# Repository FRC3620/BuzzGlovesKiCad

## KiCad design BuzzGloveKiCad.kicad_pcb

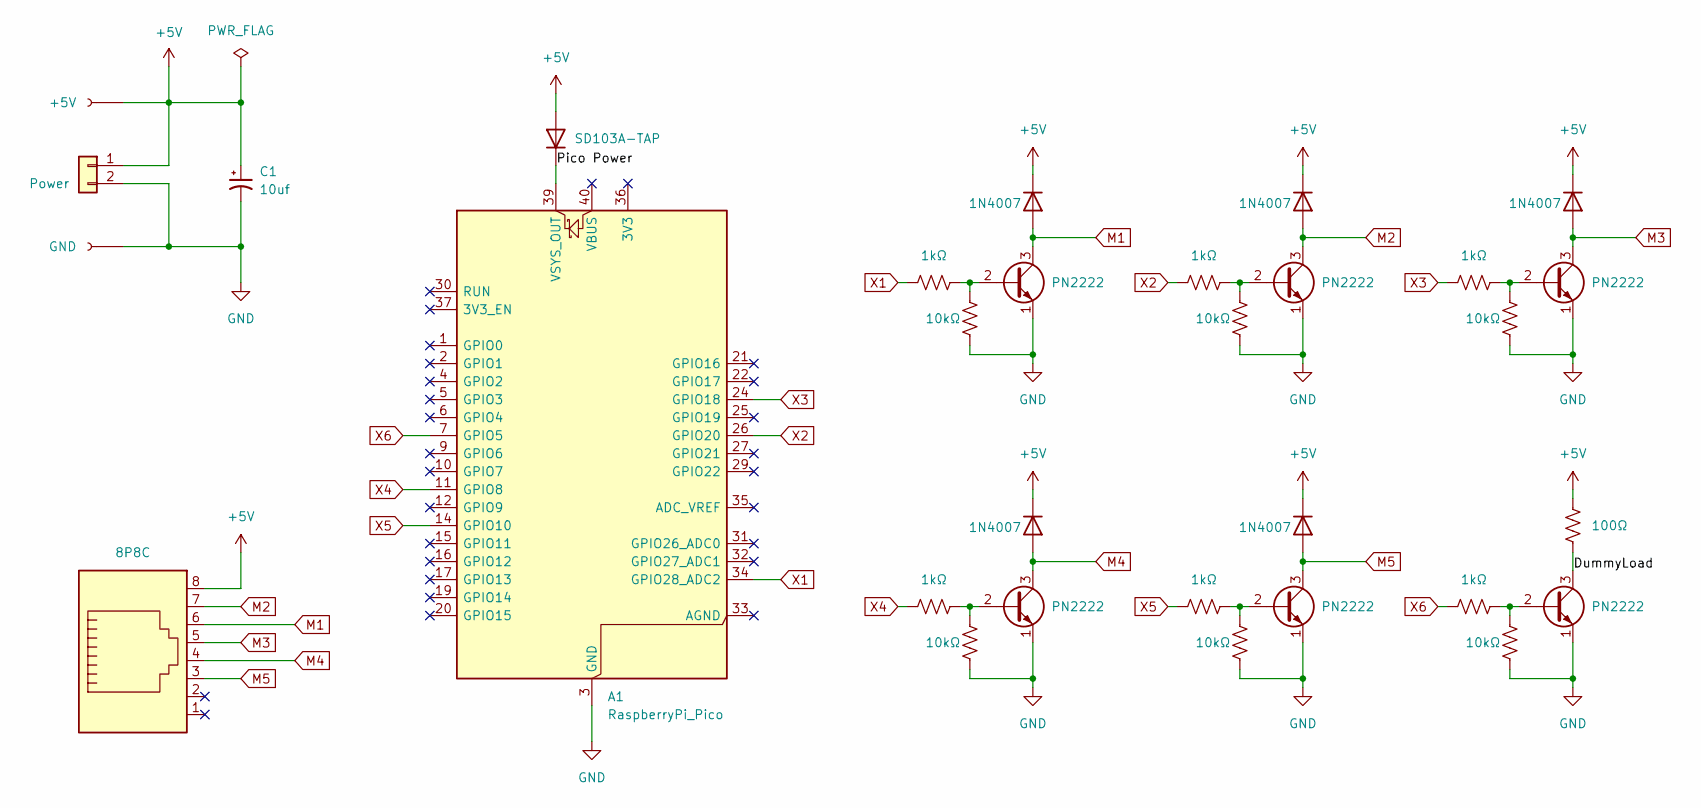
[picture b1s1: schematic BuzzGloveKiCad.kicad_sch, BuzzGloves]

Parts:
A1: RaspberryPi_Pico; RaspberryPi_Pico_Common_Unspecified
C1: 10uf; CP_Radial_D6.3mm_P2.50mm
D1: SD103A-TAP; D_DO-35_SOD27_P7.62mm_Horizontal
D2, D3, D4, D5, D6: 1N4007; D_DO-41_SOD81_P10.16mm_Horizontal
J1: +5V; Pin_D1.0mm_L10.0mm
J2: 8P8C; AMPHENOL_54602-908LF
J3: GND; Pin_D1.0mm_L10.0mm
J4: Power; JST_PH_B2B-PH-K_1x02_P2.00mm_Vertical
Q1, Q2, Q3, Q4, Q5, Q6: PN2222; TO-92
R3, R5, R7, R9, R11, R13: 1kΩ; R_Axial_DIN0204_L3.6mm_D1.6mm_P7.62mm_Horizontal
R4, R6, R8, R10, R12, R14: 10kΩ; R_Axial_DIN0204_L3.6mm_D1.6mm_P7.62mm_Horizontal
R15: 100Ω; R_Axial_DIN0207_L6.3mm_D2.5mm_P10.16mm_Horizontal

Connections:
+5V: C1.1, D1.2 (A), D2.1 (K), D3.1 (K), D4.1 (K), D5.1 (K), D6.1 (K), J1.1, J2.8, J4.1, R15.1
/DummyLoad: Q6.3 (C), R15.2; also elsewhere on the board
/Pico Power: A1.39 (VSYS_OUT), D1.1 (K)
GND: A1.3 (GND), A1.8 (GND), A1.13 (GND), A1.18 (GND), A1.23 (GND), A1.28 (GND), A1.38 (GND), C1.2, J3.1, J4.2, Q1.1 (E), Q2.1 (E), Q3.1 (E), Q4.1 (E), Q5.1 (E), Q6.1 (E), R4.2, R6.2, R8.2, R10.2, R12.2, R14.2; also elsewhere on the board
M1: D2.2 (A), J2.6, Q1.3 (C)
M2: D3.2 (A), J2.7, Q2.3 (C)
M3: D4.2 (A), J2.5, Q3.3 (C)
M4: D5.2 (A), J2.4, Q4.3 (C)
M5: D6.2 (A), J2.3, Q5.3 (C)
unnamed: Q1.2 (B), R3.1, R4.1
unnamed: Q2.2 (B), R5.1, R6.1
unnamed: Q3.2 (B), R7.1, R8.1
unnamed: Q4.2 (B), R9.1, R10.1
unnamed: Q5.2 (B), R11.1, R12.1
unnamed 14: Q6.2 (B), R13.1, R14.1; also elsewhere on the board
X1: A1.34 (GPIO28_ADC2), R3.2
X2: A1.26 (GPIO20), R5.2
X3: A1.24 (GPIO18), R7.2
X4: A1.11 (GPIO8), R9.2
X5: A1.14 (GPIO10), R11.2
X6: A1.7 (GPIO5), R13.2

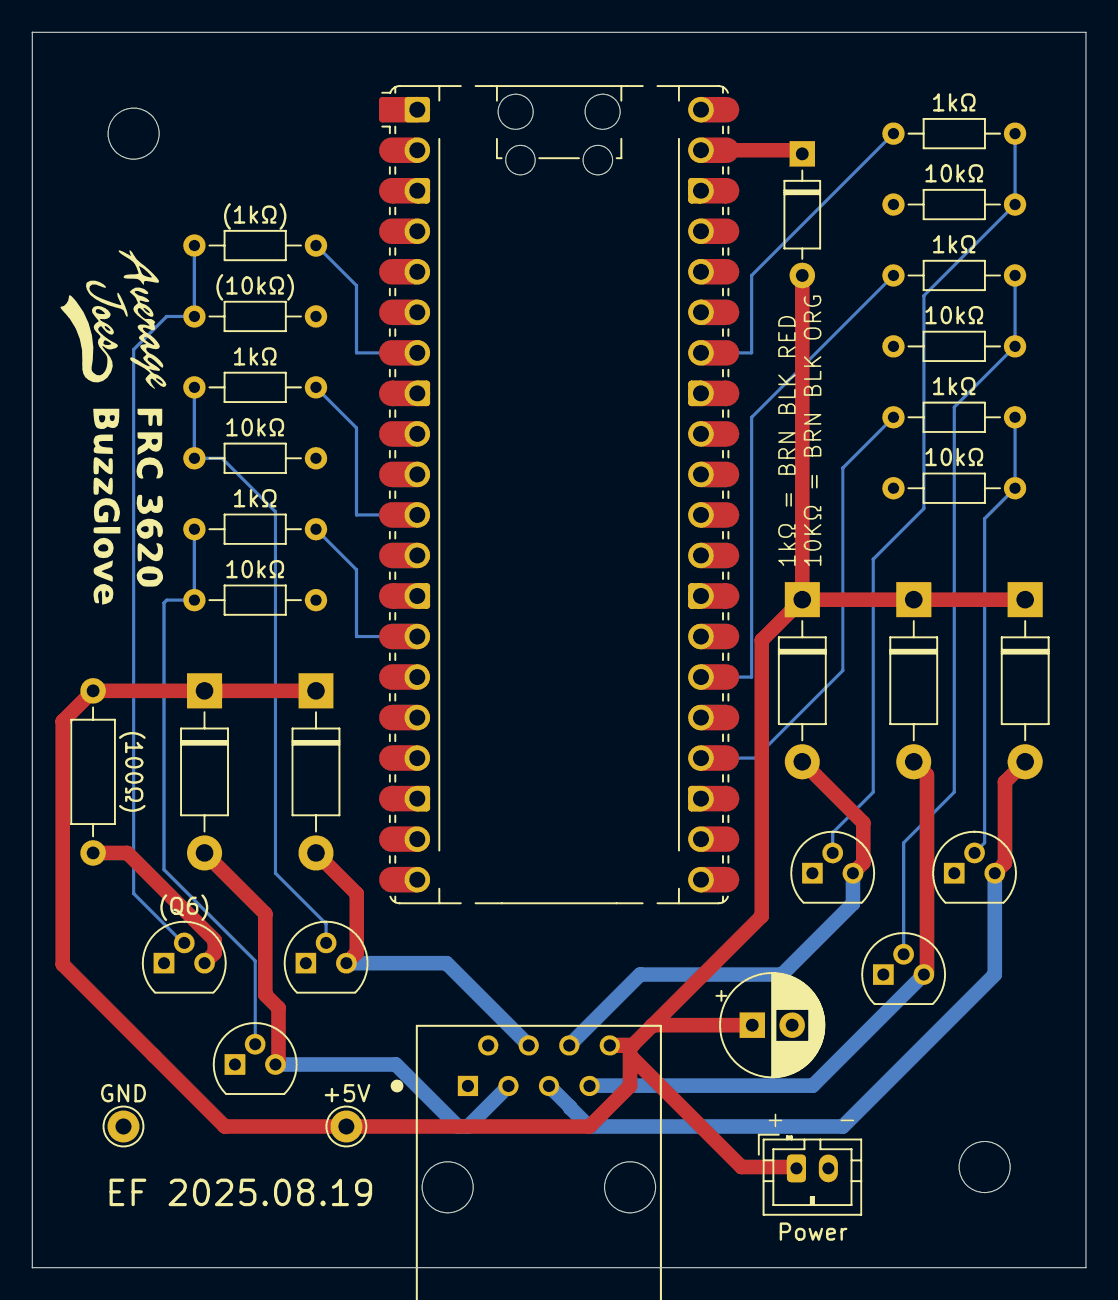
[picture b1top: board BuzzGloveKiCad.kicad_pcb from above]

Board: 2 copper layers, 66.0 x 77.4 mm, 31 parts (0 on the bottom side), 21 nets.

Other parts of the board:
(Q6): PN2222; TO-92

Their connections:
/DummyLoad: (Q6).3 (C); also elsewhere on the board
GND: (Q6).1 (E); also elsewhere on the board
unnamed 14: (Q6).2 (B); also elsewhere on the board

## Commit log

2025-04-04 Initial KiCAD version.
2025-06-24 Save version 25.04.14
2025-08-12 This is what was shipped to pcbway today.
    Small silk screen changes.
2026-02-27 Print color codes on silkscreen.
2026-03-06 Save Gerbers used on orders.
2026-03-06 Make sure we have everything.
